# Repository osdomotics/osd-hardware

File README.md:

osd-hardware
============

Hardware and Bootloaders for the OSD-Platform

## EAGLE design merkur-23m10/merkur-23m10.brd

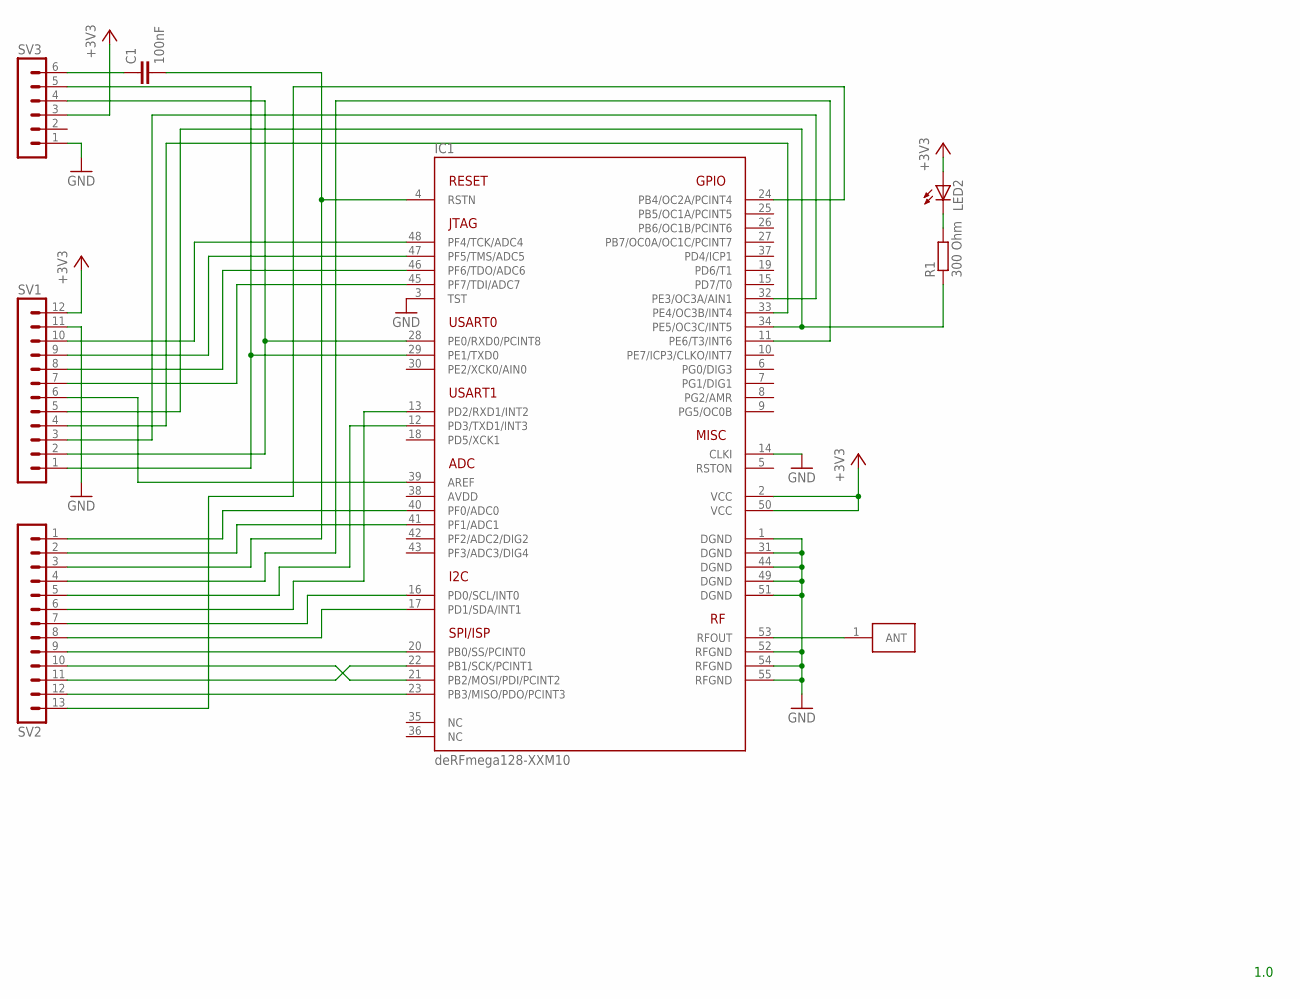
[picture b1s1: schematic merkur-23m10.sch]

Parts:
C1: 100nF; C0603
IC1: DERFMEGA128-XXM10; A-M10
LED2: LEDCHIP-LED0603; CHIP-LED0603
R1: 300 Ohm; R0603
SV1: MA12-1
SV2: MA13-1
SV3: MA06-1
U$1: PAD; FE05-1

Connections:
+3V3: IC1.2 (VCC), IC1.50 (VCC), LED2.A, SV1.12, SV3.3
GND: IC1.1 (DGND), IC1.3 (TST), IC1.14 (CLKI), IC1.31 (DGND), IC1.44 (DGND), IC1.49 (DGND), IC1.51 (DGND), IC1.52 (RFGND), IC1.54 (RFGND), IC1.55 (RFGND), SV1.11, SV3.1
unnamed: IC1.29 (PE1/TXD0), SV1.1, SV3.5
unnamed: IC1.28 (PE0/RXD0/PCINT8), SV1.2, SV3.4
unnamed: IC1.45 (PF7/TDI/ADC7), SV1.7
unnamed: IC1.46 (PF6/TDO/ADC6), SV1.8
unnamed: IC1.47 (PF5/TMS/ADC5), SV1.9
unnamed: IC1.48 (PF4/TCK/ADC4), SV1.10
unnamed: C1.2, IC1.4 (RSTN), SV2.3
unnamed: IC1.34 (PE5/OC3C/INT5), R1.1, SV1.5
unnamed: IC1.33 (PE4/OC3B/INT4), SV1.4
unnamed: IC1.32 (PE3/OC3A/AIN1), SV1.3
unnamed: IC1.17 (PD1/SDA/INT1), SV2.8
unnamed: IC1.16 (PD0/SCL/INT0), SV2.7
unnamed: IC1.20 (PB0/SS/PCINT0), SV2.9
unnamed: IC1.22 (PB1/SCK/PCINT1), SV2.11
unnamed: IC1.21 (PB2/MOSI/PDI/PCINT2), SV2.10
unnamed: IC1.23 (PB3/MISO/PDO/PCINT3), SV2.12
unnamed: IC1.13 (PD2/RXD1/INT2), SV2.6
unnamed: IC1.12 (PD3/TXD1/INT3), SV2.5
unnamed: IC1.11 (PE6/T3/INT6), SV2.4
unnamed: IC1.41 (PF1/ADC1), SV2.2
unnamed: IC1.40 (PF0/ADC0), SV2.1
unnamed: IC1.39 (AREF), SV1.6
unnamed: LED2.C, R1.2
unnamed: IC1.24 (PB4/OC2A/PCINT4), SV2.13
unnamed: C1.1, SV3.6
RFOUT: IC1.53 (RFOUT), U$1.1

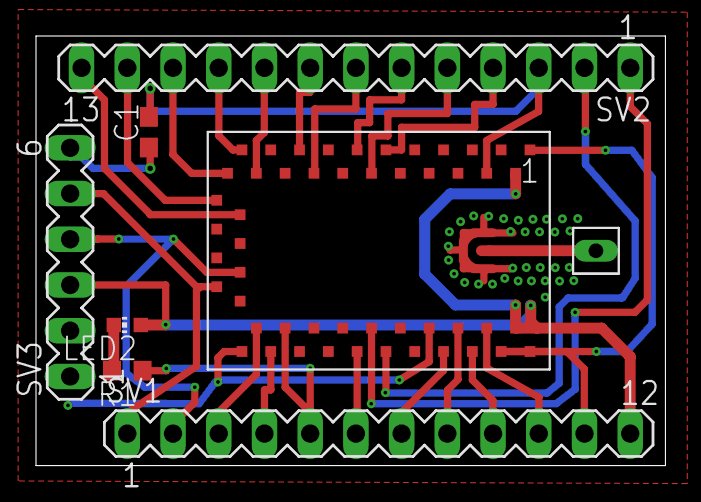
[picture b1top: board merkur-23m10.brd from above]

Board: 2 copper layers, 35.0 x 23.9 mm, 8 parts (0 on the bottom side), 28 nets.

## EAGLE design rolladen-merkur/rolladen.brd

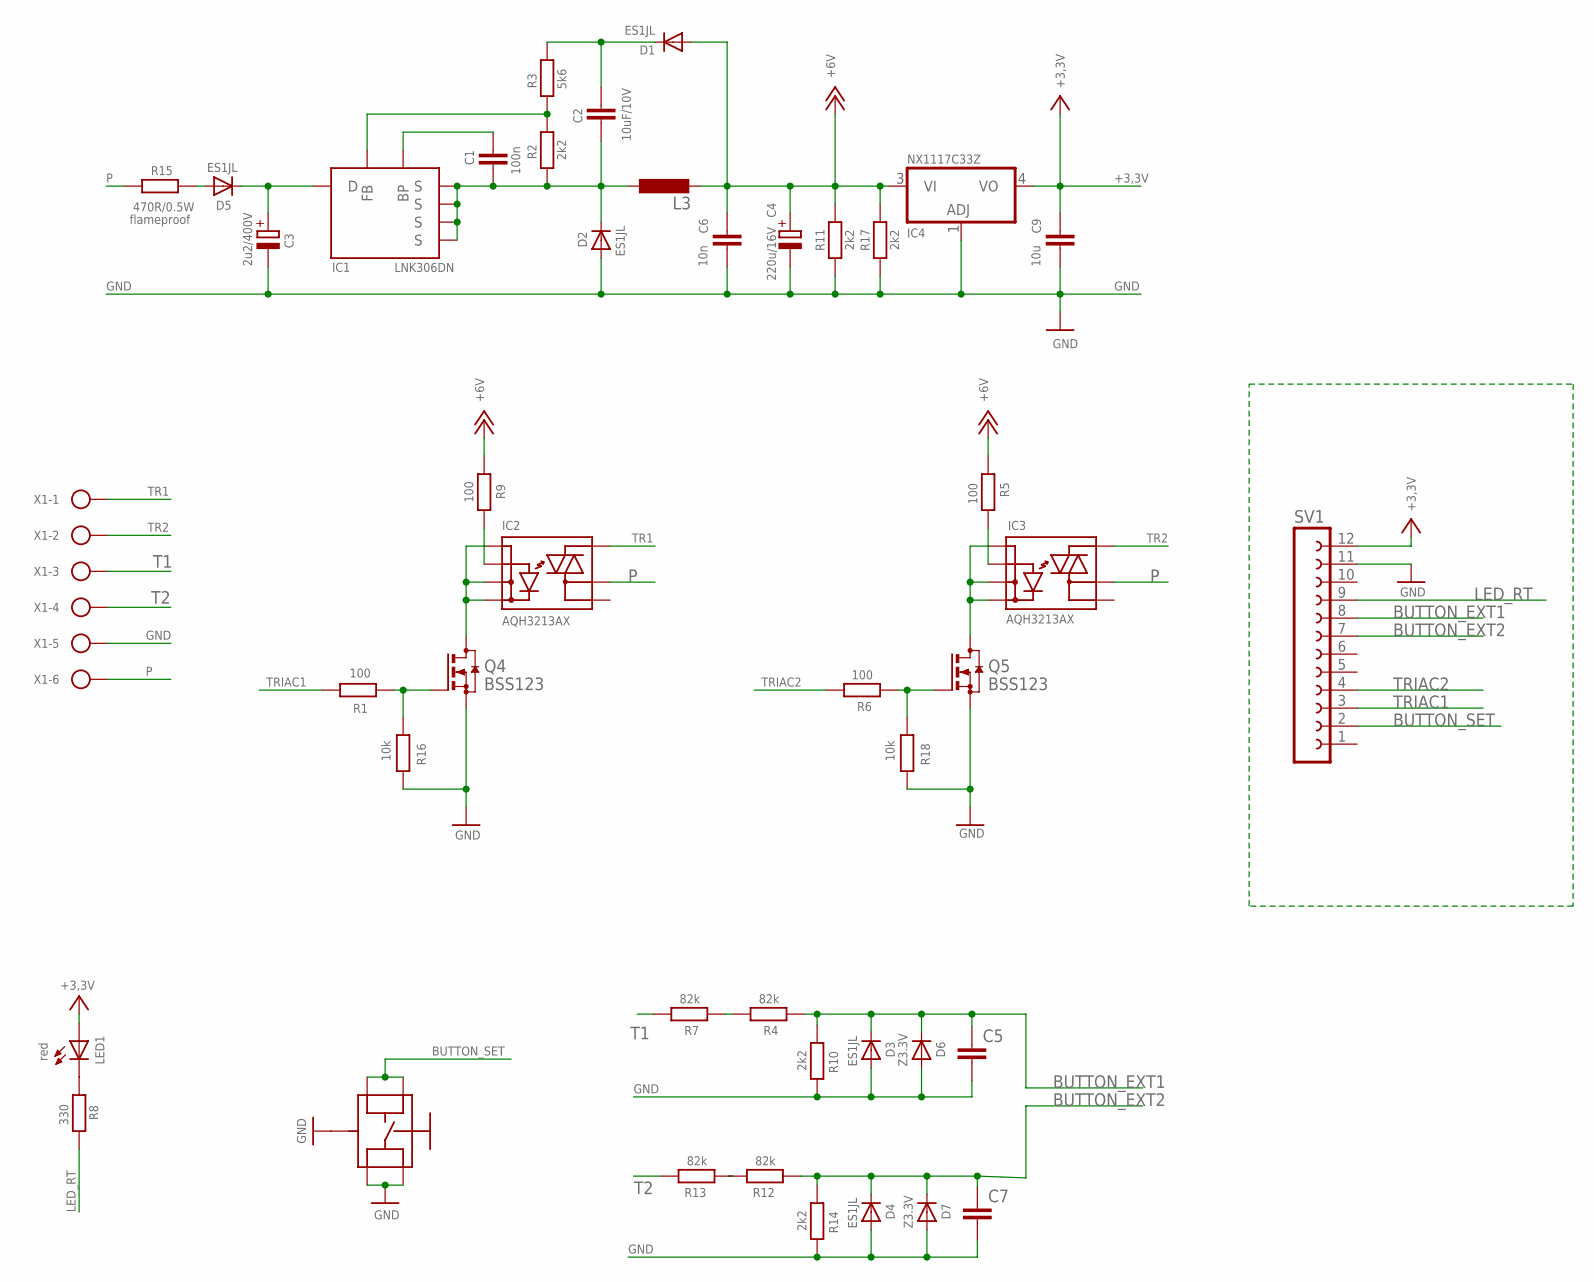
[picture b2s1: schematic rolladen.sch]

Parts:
C1: 100n; C0603
C2: 10uF/10V; C0805
C3: 2u2/400V; TT5D11L
C4: 220u/16V; 153CLV-0605
C5, C7: C-EUC0603; C0603
C6: 10n; C0603
C9: 10u; C0805
D1, D2, D3, D4, D5: ES1JL; SOD323-W
D6, D7: Z3.3V; SOD323-W
IC1: LNK306DN; SO-8C
IC2, IC3: AQH3213AX; SO-08D
IC4: NX1117C33Z; SOT223
L3: L-EUWE-TPC; POWER-CHOKE_WE-TPC
LED1: red; CHIPLED_0603
Q4, Q5: BSS123; SOT23
R1, R5, R6, R9: 100; R0603
R2, R10, R11, R14, R17: 2k2; R0603
R3: 5k6; R0603
R4, R7, R12, R13: 82k; R0805
R8: 330; R0603
R15: 470R/0.5W; 0411V
R16, R18: 10k; R0603
S1: KMR
SV1: FE12-1; FE12
X1: W237-06P; W237-6P

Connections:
+3,3V: C9.1, IC4.4 (VO), LED1.A, SV1.12
+12V: C4.+, C6.1, D1.A, IC4.3 (VI), L3.2, R5.1, R9.1, R11.2, R17.2
BUTTON_EXT1: C5.1, D3.C, D6.C, R4.1, R10.1, SV1.8
BUTTON_EXT2: C7.1, D4.C, D7.C, R12.1, R14.1, SV1.7
BUTTON_SET: S1.P$2, S1.P$3, SV1.2
GND: C3.-, C4.-, C5.2, C6.2, C7.2, C9.2, D2.A, D3.A, D4.A, D6.A, D7.A, IC4.1 (ADJ), Q4.2 (S), Q5.2 (S), R10.2, R11.1, R14.2, R16.2, R17.1, R18.2, S1.P$1, S1.P$4, S1.P$5, SV1.11, X1.5
LED_RT: R8.2, SV1.9
unnamed: IC1.P$2 (FB), R2.2, R3.1
unnamed: C1.1, IC1.P$1 (BP)
unnamed: C1.2, C2.2, D2.C, IC1.P$4 (S), IC1.P$5 (S), IC1.P$6 (S), IC1.P$7 (S), L3.1, R2.1
unnamed: C2.1, D1.C, R3.2
unnamed: D5.A, R15.1
unnamed: IC2.P$1, IC2.P$3, IC2.P$4, Q4.3 (D)
unnamed: R4.2, R7.1
unnamed: Q4.1 (G), R1.1, R16.1
unnamed: IC3.P$2, R5.2
unnamed: IC3.P$1, IC3.P$3, IC3.P$4, Q5.3 (D)
unnamed: LED1.C, R8.1
unnamed: Q5.1 (G), R6.1, R18.1
unnamed: R12.2, R13.1
unnamed: IC2.P$2, R9.2
unnamed: C3.+, D5.C, IC1.P$3 (D)
P: IC2.P$6, IC3.P$6, R15.2, X1.6
T1: R7.2, X1.3
T2: R13.2, X1.4
TR1: IC2.P$7, X1.1
TR2: IC3.P$7, X1.2
TRIAC1: R1.2, SV1.3
TRIAC2: R6.2, SV1.4

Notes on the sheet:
flameproof

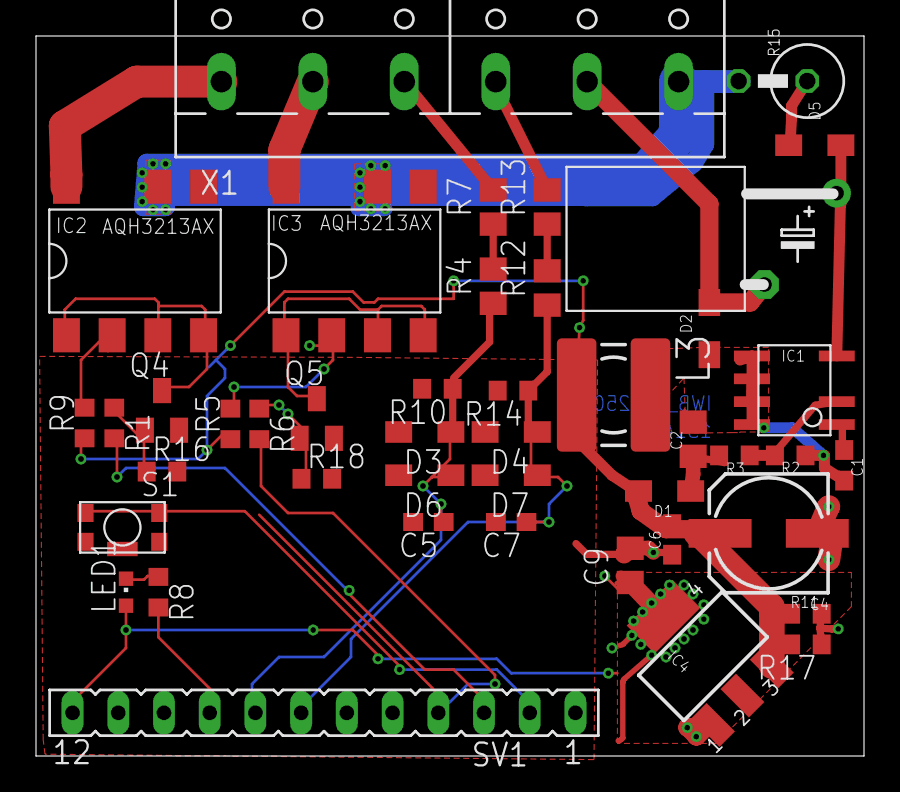
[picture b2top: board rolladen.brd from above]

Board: 2 copper layers, 46.0 x 40.0 mm, 44 parts (0 on the bottom side), 29 nets.

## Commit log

2012-10-04 initial upload
2012-10-05 Bootloader at 1F000 change fuses
2012-10-08 change fuses order
2012-12-13 bugfix AVDD, add pin13 PB4 PCINT4 -> configuration pin
2012-12-13 bugfix scaling
2013-02-04 bugfix overlap
2013-06-03 Commit initial upload
2013-06-03 add get_mac function
2013-06-04 get_mac read far
2013-06-11 bugfix: add make clean
2014-04-15 added
2014-04-17 add arduino definition files
2014-04-18 define merkur pins
2014-04-18 merkurboard pins definition
2014-04-22 new name Merkur Dev Board
2014-05-07 README update
    Use README.rst as name (ReStructured Text) for nicer rendering by
    github.
2014-05-12 New version with jump table
    We now generate a jump table for calling the get_mac routine from an
    application. Note that we use some padding to *also* have the real
    _get_mac routine at the old location with the new compiler of debian
    squeeze. For details see README.rst.
2014-05-13 Add missing file, fix comment
2014-05-13 Allow '-' (in addition to ':') in MAC
2014-05-26 disable JTAG to use the i/o as digital pins
2014-05-26 bugfix read-analog
2014-07-15 inital opload
2015-03-08 bugfix arduino name
2015-03-08 cleanup
2016-02-17 inital upload
2016-02-18 bugfix make isp
2016-02-19 bugfix replace mac from - to :
2017-01-16 Add .gitignore
    Ignore generated files so it's easier to track changes
2018-03-30 make display lenght space 1mm larger
2018-04-04 add Display cable space
2018-04-05 add e-paper sanp
2018-04-05 improved printability, added merkurboard holders
2018-04-06 make snap space greater, make display cable space greater
2018-04-07 fixed display module,added version with slots for touch sensors - https://www.amazon.de/dp/B01MU3K7Z5/
2018-04-08 improved (wall thickness)
2018-04-09 make longer space for flat cabel; more space for snap element
2018-04-12 change batterie direction and longer wallholder
2018-05-02 first printout
2018-05-03 add sensor space
2018-05-04 add sensor place holder
2018-05-05 add sensor snap 1mm
2018-05-05 bufix snesor snap with a cylinder
2018-05-08 cleanup sensor space
2018-05-09 bugfix top snaps
2018-05-09 bugfix batterie space
2018-05-09 cleanup snap
2018-05-11 bugfix top hight
2018-05-11 bugfix cylinder
2018-05-14 bugfix top snap
2018-05-22 add usb_eth and usb_sdcard hole
2018-05-24 smaler for merkurboard
2018-05-25 bugfix case holders Merkurboard, bugfix case wide
2018-05-26 added
    added
2018-05-27 bugfix dicknes , placeholder orange-pi, placeholder merkurboard
2018-05-28 bugfix snaps
2018-05-30 add holders, bugfix holes
2018-05-30 bugfix orange pi holder
2018-06-01 bugfix eth hole
2018-06-02 bugfix top stability
2018-06-17 bugfix holes
2018-06-23 bugfix merkurbord holder
2018-07-02 added flag to generate it with or without touch btns
